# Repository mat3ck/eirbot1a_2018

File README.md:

# eirbot1a_2018

Eirbot first year team project for 2018 France Championship of Robotics 
___
Projet de l'equipe 1A d'Eirbot pour la coupe de France de robotique 2018

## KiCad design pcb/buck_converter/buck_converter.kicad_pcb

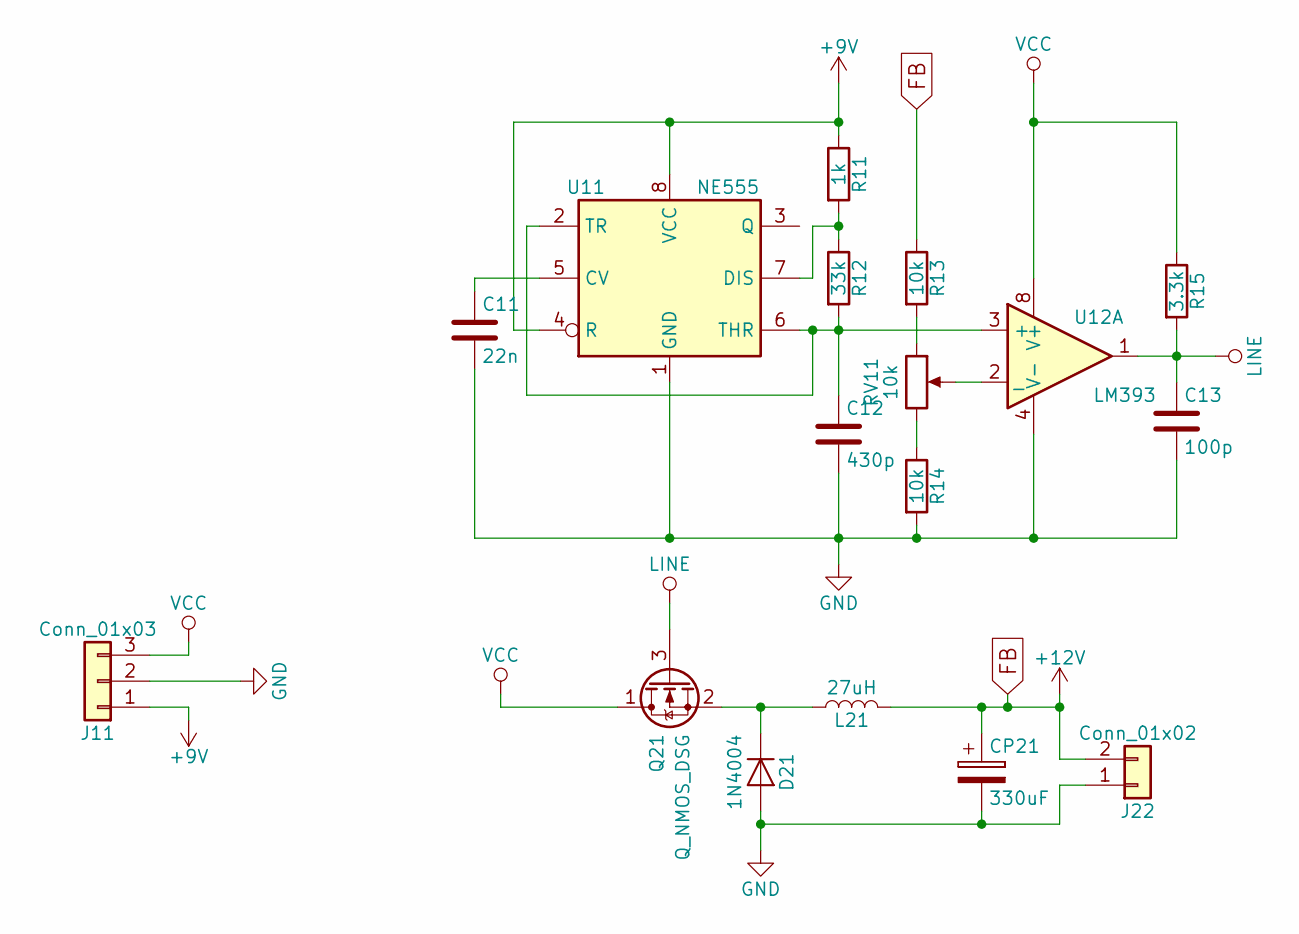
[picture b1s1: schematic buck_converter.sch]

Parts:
C11: 22n; C_0805_HandSoldering
C12: 430p; C_Disc_D4.7mm_W2.5mm_P5.00mm
C13: 100p; C_0805_HandSoldering
CP21: 330uF; CP_Radial_D10.0mm_P5.00mm
D21: 1N4004; D_A-405_P10.16mm_Horizontal
J11: Conn_01x03; PhoenixContact_MC-G_03x3.81mm_Angled
J22: Conn_01x02; PhoenixContact_MC-G_02x3.81mm_Angled
L21: 27uH; L_Radial_D8.7mm_P5.00mm_Fastron_07HCP
Q21: Q_NMOS_DSG; TO-220-3_Vertical
R11: 1k; R_0805_HandSoldering
R12: 33k; R_0805_HandSoldering
R13, R14: 10k; R_0805_HandSoldering
R15: 3.3k; R_0805_HandSoldering
RV11: 10k; Potentiometer_Trimmer_Bourns_3296Y
U11: NE555; DIP-8_W7.62mm_LongPads
U12: LM393; DIP-8_W7.62mm_LongPads

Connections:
+9V: J11.1, R11.1, U11.4 (R), U11.8 (VCC)
FB: CP21.1, J22.2, L21.2, R13.1
GND: C11.2, C12.2, C13.2, CP21.2, D21.2 (A), J11.2, J22.1, R14.2, U11.1 (GND), U12.4 (V-)
LINE: C13.1, Q21.3 (G), R15.2, U12.1
unnamed: C11.1, U11.5 (CV)
unnamed: C12.1, R12.2, U11.2 (TR), U11.6 (THR), U12.3 (+)
unnamed: D21.1 (K), L21.1, Q21.2 (S)
unnamed: R11.2, R12.1, U11.7 (DIS)
unnamed: R13.2, RV11.1
unnamed: R14.1, RV11.3
unnamed: RV11.2, U12.2 (_)
VCC: J11.3, Q21.1 (D), R15.1, U12.8 (V+)

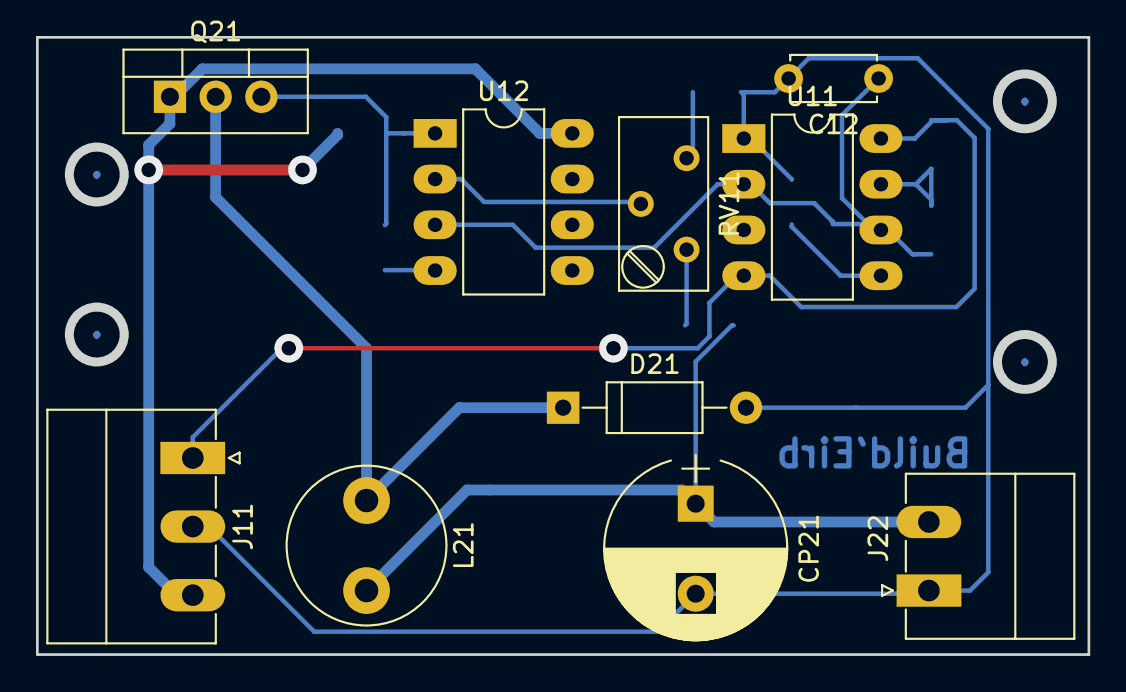
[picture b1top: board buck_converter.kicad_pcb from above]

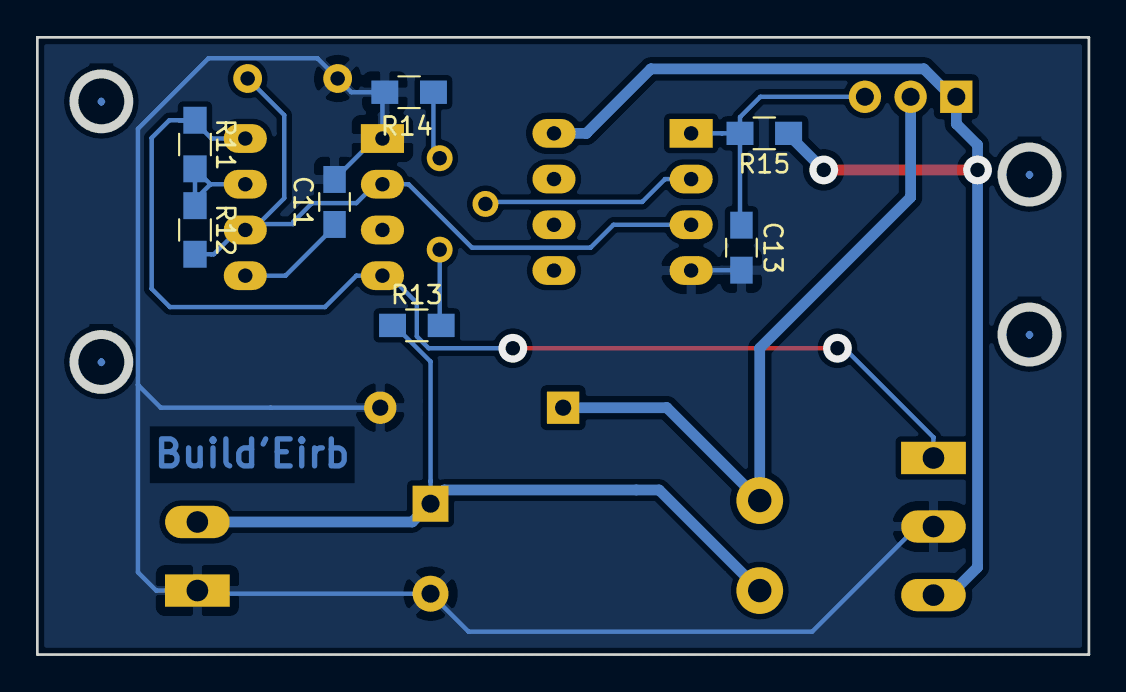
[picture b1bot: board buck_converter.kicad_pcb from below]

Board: 2 copper layers, 58.4 x 34.3 mm, 17 parts (7 on the bottom side), 12 nets.

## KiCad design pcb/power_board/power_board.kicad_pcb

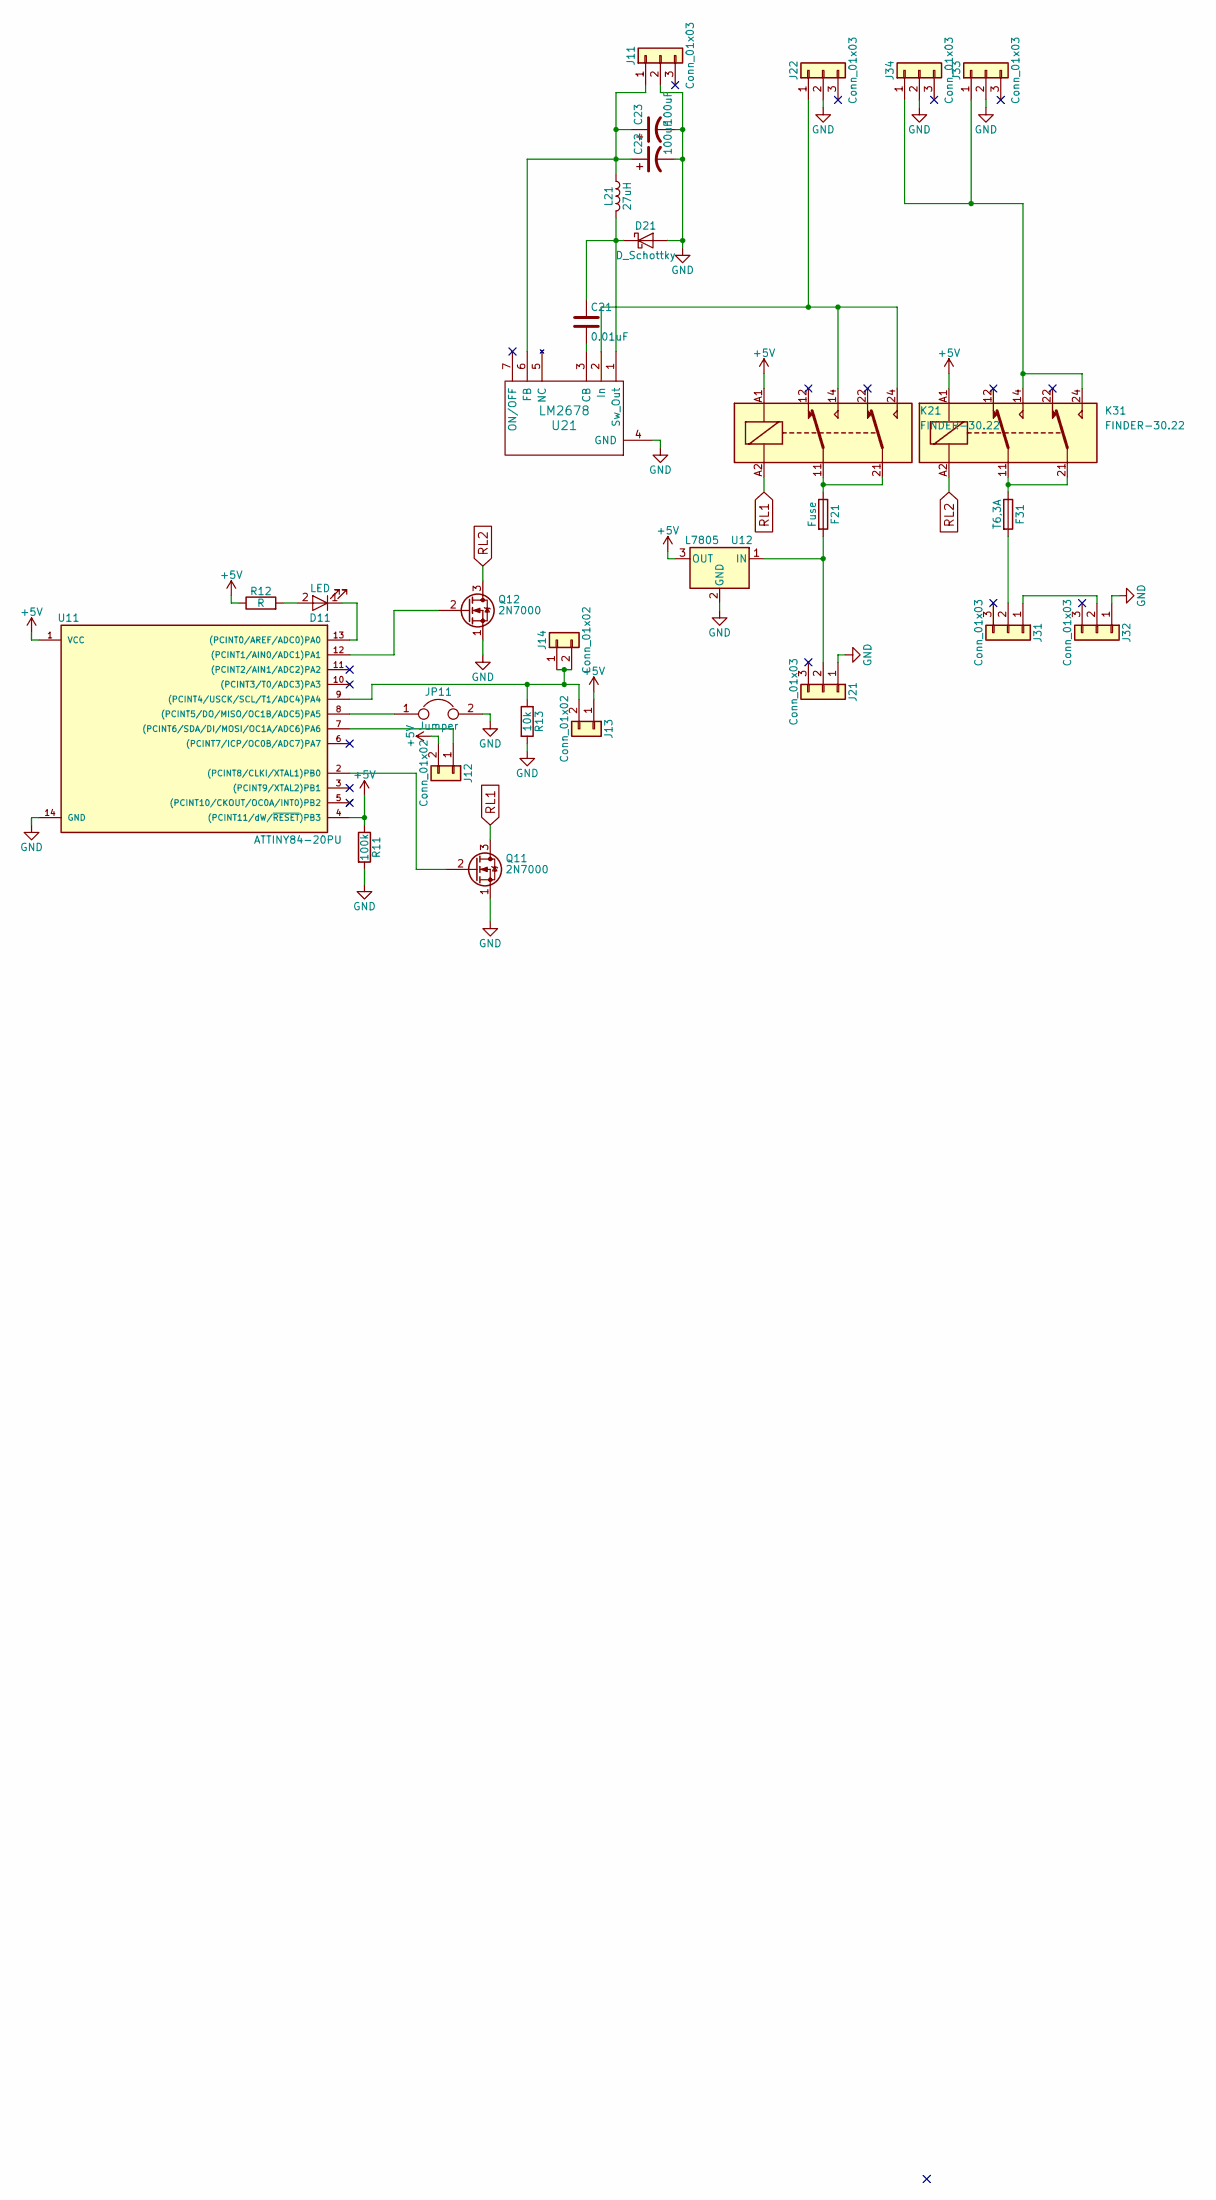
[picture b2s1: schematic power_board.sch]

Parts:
C21: 0.01uF; C_Disc_D4.3mm_W1.9mm_P5.00mm
C22, C23: 100uF; CP_Radial_D6.3mm_P2.50mm
D11: LED; LED_1206_HandSoldering
D21: D_Schottky; D_DO-41_SOD81_P7.62mm_Horizontal
F21: Fuse; Fuseholder5x20_horiz_open_inline_Type-I
F31: T6,3A; Fuseholder5x20_horiz_open_inline_Type-I
J11, J21, J22, J31, J32, J33, J34: Conn_01x03; PhoenixContact_MC-G_03x3.81mm_Angled
J12, J13: Conn_01x02; PhoenixContact_MC-G_02x3.81mm_Angled
J14: Conn_01x02; Pin_Header_Straight_1x02_Pitch2.54mm
JP11: Jumper; Test_Point_2Pads
K21, K31: FINDER-30.22; Relay_DPDT_Finder_40.52
L21: 27uH; L_Radial_D7.8mm_P5.00mm_Fastron_07HCP
Q11, Q12: 2N7000; TO-92_Molded_Narrow
R11: 100k; R_0805_HandSoldering
R12: R; R_0805_HandSoldering
R13: 10k; R_0805_HandSoldering
U11: ATTINY84-20PU; DIP-14_W7.62mm
U12: L7805; TO-220-3_Vertical
U21: LM2678; TO-220-7_Vertical_StaggeredType1

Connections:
+5V: J12.2, J13.1, K21.A1, K31.A1, R11.1, R12.1, U11.1 (VCC), U11.4 ((PCINT11/dW/~RESET~)PB3), U12.3 (OUT)
GND: C22.2, C23.2, D21.2 (A), J11.2, J21.1, J22.2, J32.1, J33.2, J34.2, JP11.2, Q11.1 (S), Q12.1 (S), R11.2, R13.2, U11.14 (GND), U12.2 (GND), U21.4 (GND)
unnamed: C21.1, D21.1 (K), L21.2, U21.1 (Sw_Out)
unnamed: C21.2, U21.3 (CB)
unnamed: C22.1, C23.1, J11.1, L21.1, U21.6 (FB)
unnamed: D11.1 (K), U11.13 ((PCINT0/AREF/ADC0)PA0)
unnamed: D11.2 (A), R12.2
unnamed: F21.1, K21.11, K21.21
unnamed: F21.2, J21.2, U12.1 (IN)
unnamed: F31.1, K31.11, K31.21
unnamed: F31.2, J31.2
unnamed: J12.1, U11.7 ((PCINT6/SDA/DI/MOSI/OC1A/ADC6)PA6)
unnamed: J13.2, J14.1, J14.2, R13.1, U11.9 ((PCINT4/USCK/SCL/T1/ADC4)PA4)
unnamed: J22.1, K21.14, K21.24, U21.2 (In)
unnamed: J31.1, J32.2
unnamed: J33.1, J34.1, K31.14, K31.24
unnamed: JP11.1, U11.8 ((PCINT5/DO/MISO/OC1B/ADC5)PA5)
unnamed: Q11.2 (G), U11.2 ((PCINT8/CLKI/XTAL1)PB0)
unnamed: Q12.2 (G), U11.12 ((PCINT1/AIN0/ADC1)PA1)
RL1: K21.A2, Q11.3 (D)
RL2: K31.A2, Q12.3 (D)

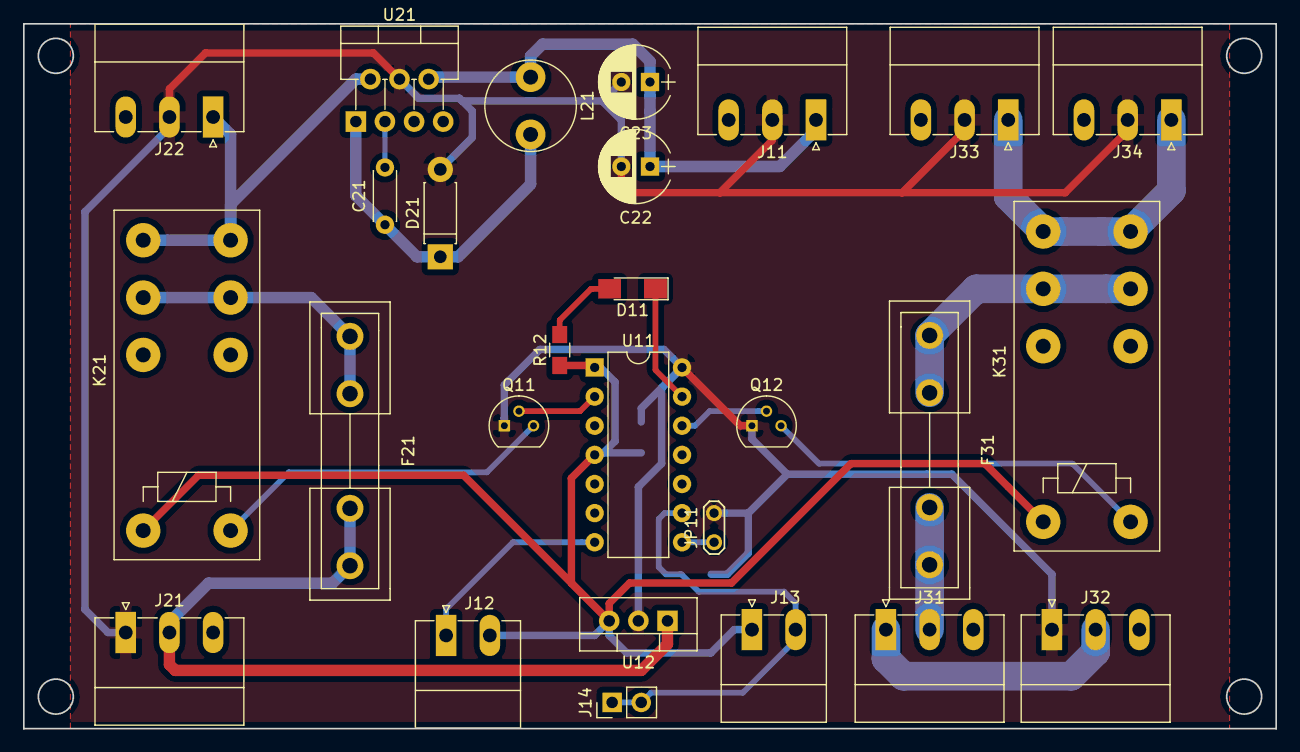
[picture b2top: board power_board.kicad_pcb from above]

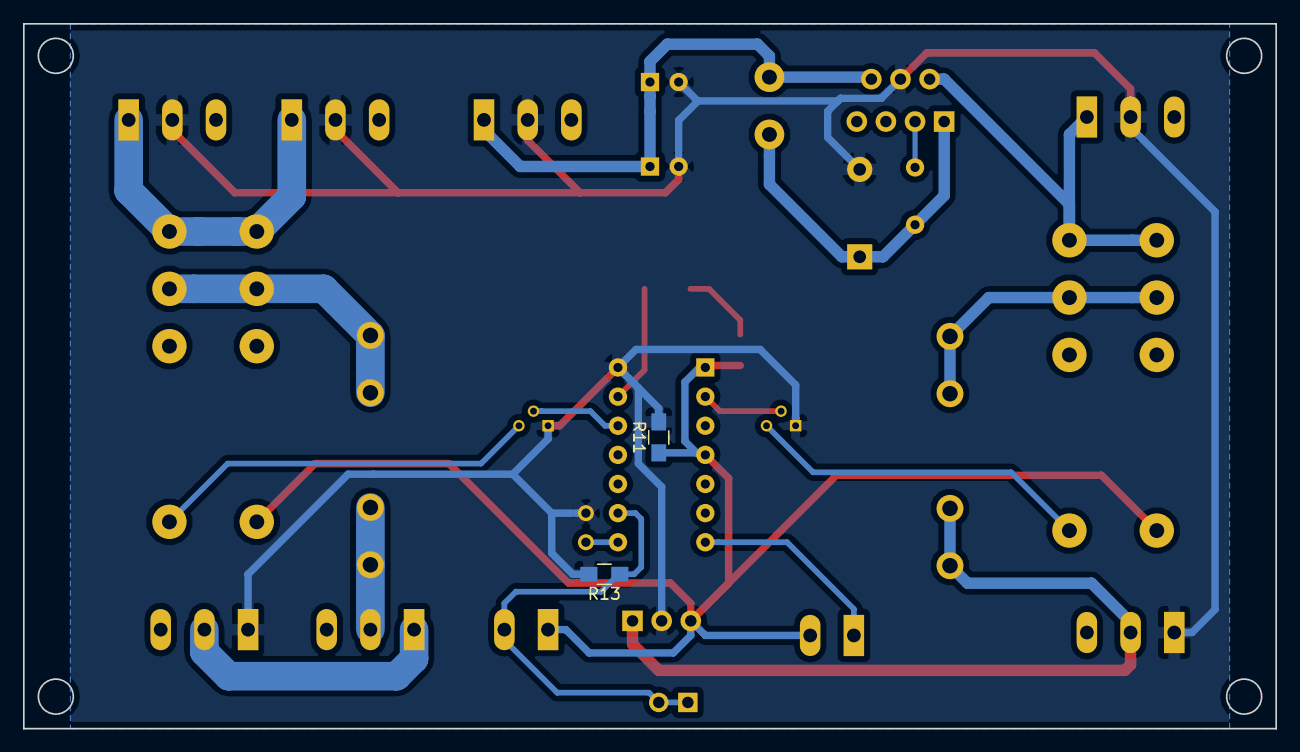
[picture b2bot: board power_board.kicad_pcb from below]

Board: 2 copper layers, 109.2 x 61.5 mm, 29 parts (2 on the bottom side), 21 nets.

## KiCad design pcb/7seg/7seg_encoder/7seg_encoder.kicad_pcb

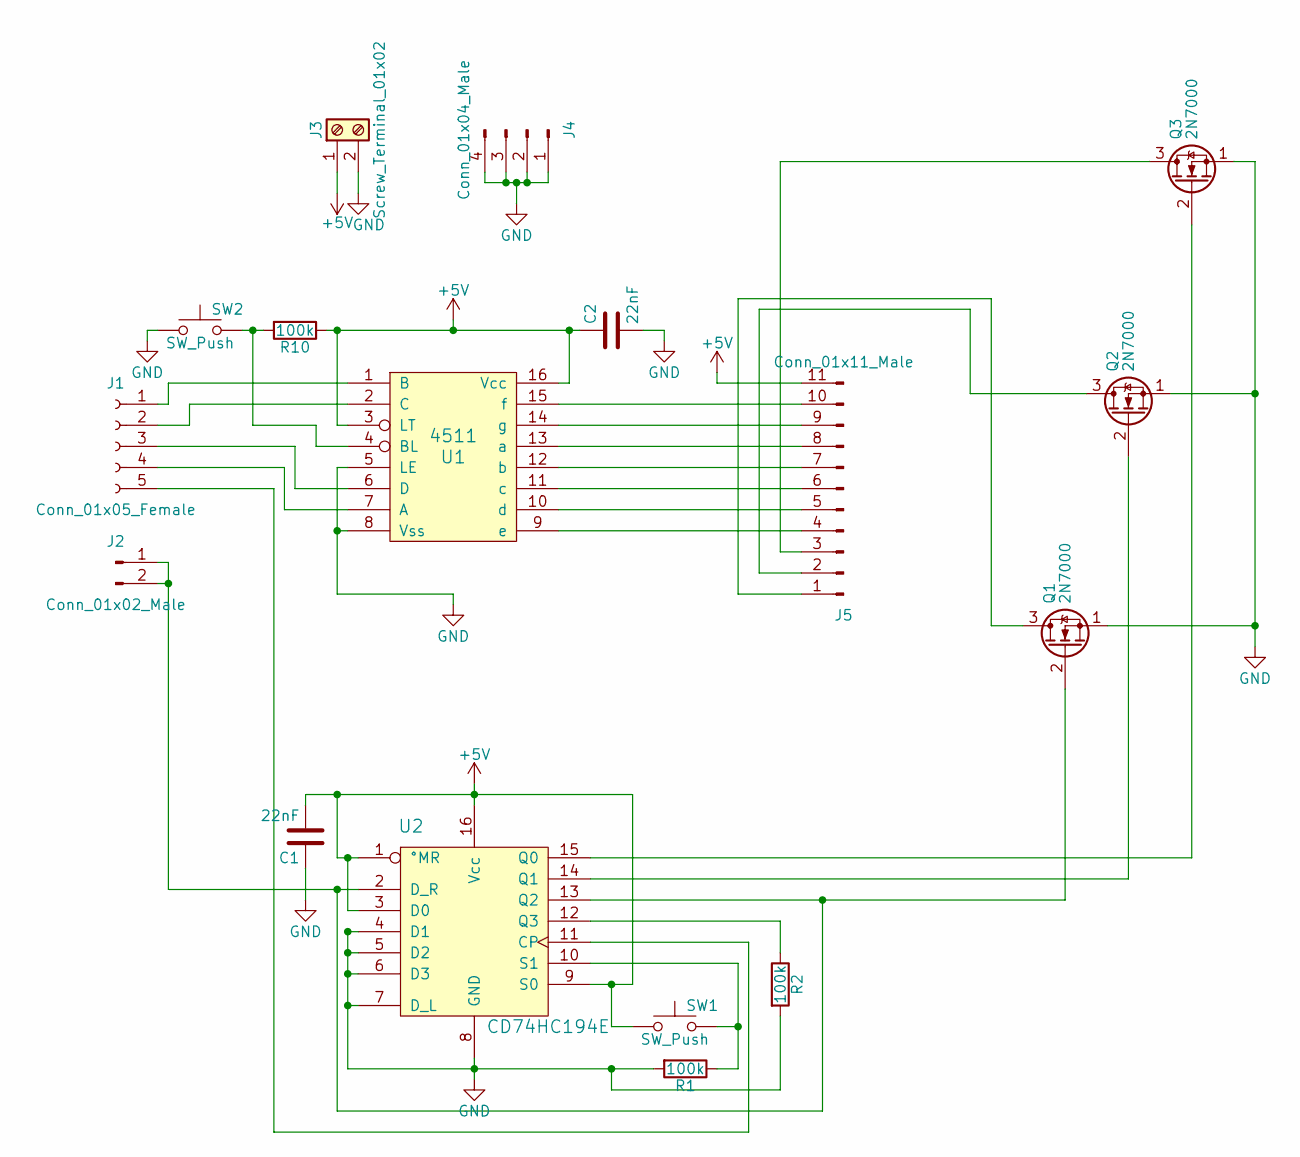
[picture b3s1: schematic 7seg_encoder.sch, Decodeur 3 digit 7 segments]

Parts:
C1, C2: 22nF; C_Disc_D4.3mm_W1.9mm_P5.00mm
J1: Conn_01x05_Female; Socket_Strip_Angled_1x05_Pitch2.54mm
J2: Conn_01x02_Male; Pin_Header_Angled_1x02_Pitch2.54mm
J3: Screw_Terminal_01x02; TerminalBlock_Phoenix_MPT-2.54mm_2pol
J4: Conn_01x04_Male; Pin_Header_Straight_1x04_Pitch2.54mm
J5: Conn_01x11_Male; Pin_Header_Straight_1x11_Pitch2.54mm
Q1, Q2, Q3: 2N7000; TO-92_Molded_Wide
R1, R2, R10: 100k; R_Axial_DIN0204_L3.6mm_D1.6mm_P7.62mm_Horizontal
SW1, SW2: SW_Push; SW_PUSH_6mm
U1: 4511; DIP-16_W7.62mm_Socket
U2: CD74HC194E; SOIC-16_3.9x9.9mm_Pitch1.27mm

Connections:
+5V: C1.2, C2.1, J3.1, J5.11, R10.1, SW1.1, U1.3 (LT), U1.16 (Vcc), U2.1 (°MR), U2.3 (D0), U2.9 (S0), U2.16 (Vcc)
GND: C1.1, C2.2, J3.2, J4.1, J4.2, J4.3, J4.4, Q1.1 (S), Q2.1 (S), Q3.1 (S), R1.2, R2.2, SW2.1, U1.5 (LE), U1.8 (Vss), U2.4 (D1), U2.5 (D2), U2.6 (D3), U2.7 (D_L), U2.8 (GND)
unnamed: J1.1, U1.1 (B)
unnamed: J1.2, U1.2 (C)
unnamed: J1.3, U1.6 (D)
unnamed: J1.4, U1.7 (A)
unnamed: J1.5, U2.11 (CP)
unnamed: J2.1, J2.2, Q1.2 (G), U2.2 (D_R), U2.13 (Q2)
unnamed: J5.1, Q1.3 (D)
unnamed: J5.2, Q2.3 (D)
unnamed: J5.3, Q3.3 (D)
unnamed: J5.4, U1.9 (e)
unnamed: J5.5, U1.10 (d)
unnamed: J5.6, U1.11 (c)
unnamed: J5.7, U1.12 (b)
unnamed: J5.8, U1.13 (a)
unnamed: J5.9, U1.14 (g)
unnamed: J5.10, U1.15 (f)
unnamed: Q2.2 (G), U2.14 (Q1)
unnamed: Q3.2 (G), U2.15 (Q0)
unnamed: R1.1, SW1.2, U2.10 (S1)
unnamed: R2.1, U2.12 (Q3)
unnamed: R10.2, SW2.2, U1.4 (BL)

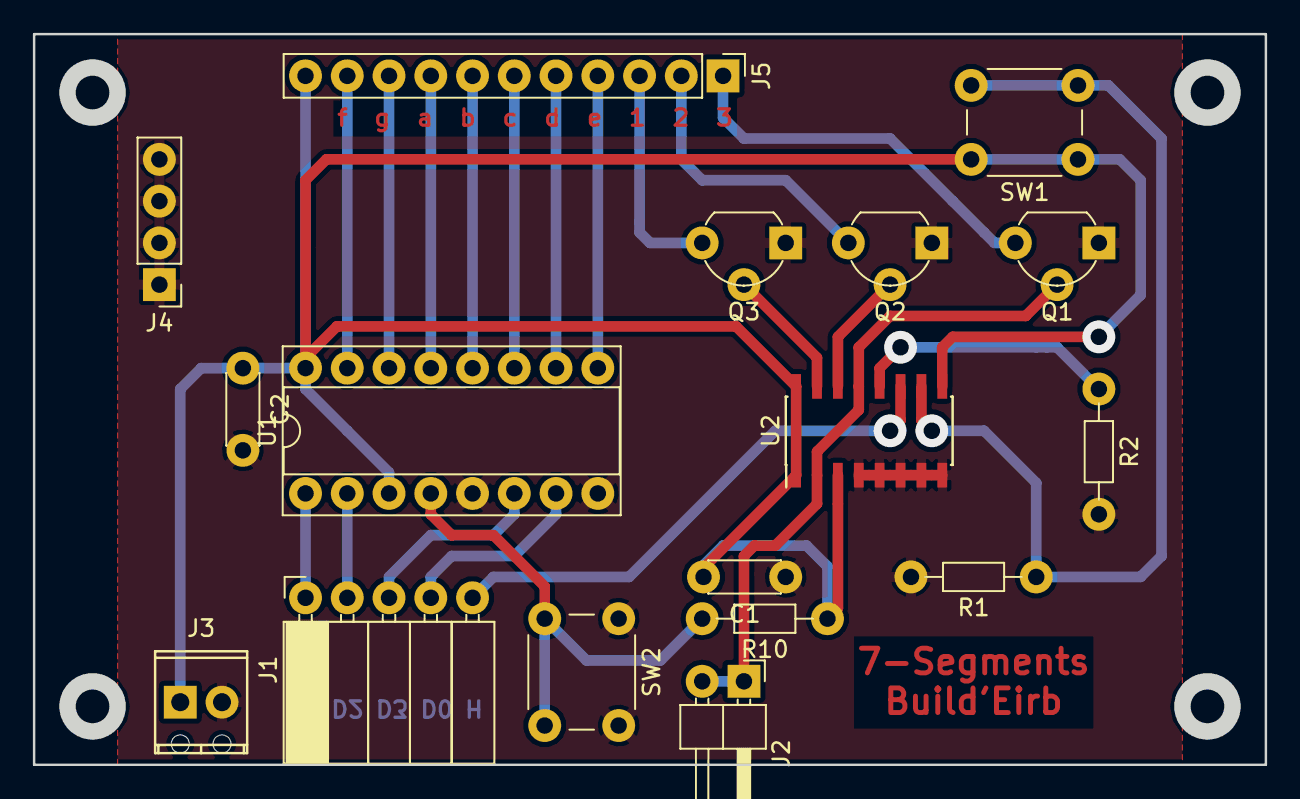
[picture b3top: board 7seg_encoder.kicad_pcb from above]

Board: 2 copper layers, 74.9 x 44.5 mm, 17 parts (0 on the bottom side), 23 nets.

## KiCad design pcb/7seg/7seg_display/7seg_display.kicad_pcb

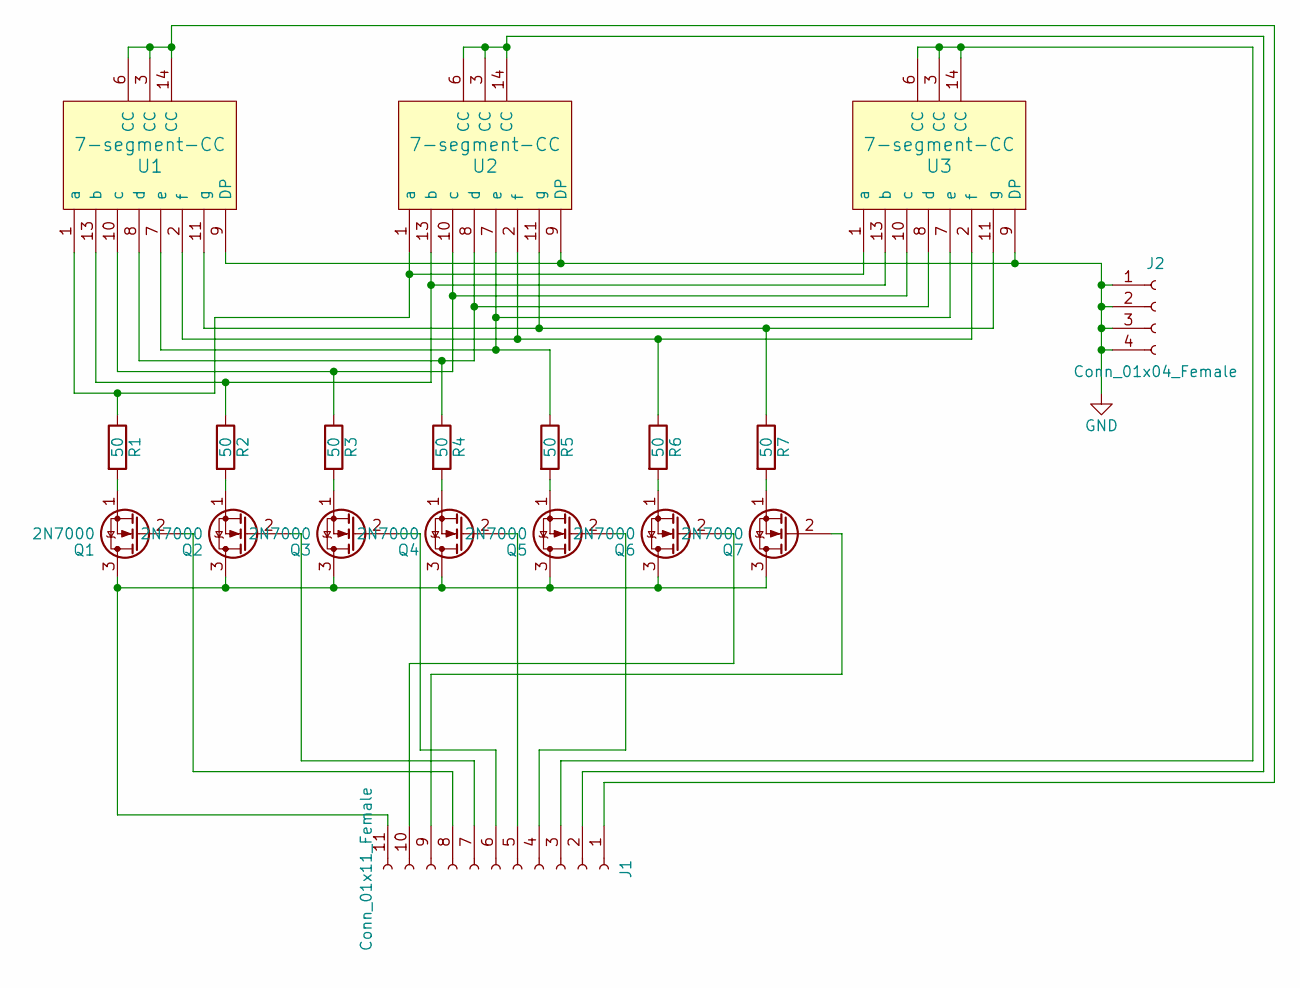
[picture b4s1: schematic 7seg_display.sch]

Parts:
J1: Conn_01x11_Female; Socket_Strip_Straight_1x11_Pitch2.54mm
J2: Conn_01x04_Female; Socket_Strip_Straight_1x04_Pitch2.54mm
Q1, Q2, Q3, Q4, Q5, Q6, Q7: 2N7000; TO-92_Molded_Wide
R1, R2, R3, R4, R5, R6, R7: 50; R_0805_HandSoldering
U1, U2, U3: 7-segment-CC; 7-segment_CC

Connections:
GND: J2.1, J2.2, J2.3, J2.4, U1.9 (DP), U2.9 (DP), U3.9 (DP)
unnamed: J1.1, U1.3 (CC), U1.6 (CC), U1.14 (CC)
unnamed: J1.2, U2.3 (CC), U2.6 (CC), U2.14 (CC)
unnamed: J1.3, U3.3 (CC), U3.6 (CC), U3.14 (CC)
unnamed: J1.4, Q5.2 (G)
unnamed: J1.5, Q4.2 (G)
unnamed: J1.6, Q3.2 (G)
unnamed: J1.7, Q2.2 (G)
unnamed: J1.8, Q1.2 (G)
unnamed: J1.9, Q7.2 (G)
unnamed: J1.10, Q6.2 (G)
unnamed: J1.11, Q1.3 (D), Q2.3 (D), Q3.3 (D), Q4.3 (D), Q5.3 (D), Q6.3 (D), Q7.3 (D)
unnamed: Q1.1 (S), R1.2
unnamed: Q2.1 (S), R2.2
unnamed: Q3.1 (S), R3.2
unnamed: Q4.1 (S), R4.2
unnamed: Q5.1 (S), R5.2
unnamed: Q6.1 (S), R6.2
unnamed: Q7.1 (S), R7.2
unnamed: R1.1, U1.1 (a), U2.1 (a), U3.1 (a)
unnamed: R2.1, U1.13 (b), U2.13 (b), U3.13 (b)
unnamed: R3.1, U1.10 (c), U2.10 (c), U3.10 (c)
unnamed: R4.1, U1.8 (d), U2.8 (d), U3.8 (d)
unnamed: R5.1, U1.7 (e), U2.7 (e), U3.7 (e)
unnamed: R6.1, U1.2 (f), U2.2 (f), U3.2 (f)
unnamed: R7.1, U1.11 (g), U2.11 (g), U3.11 (g)

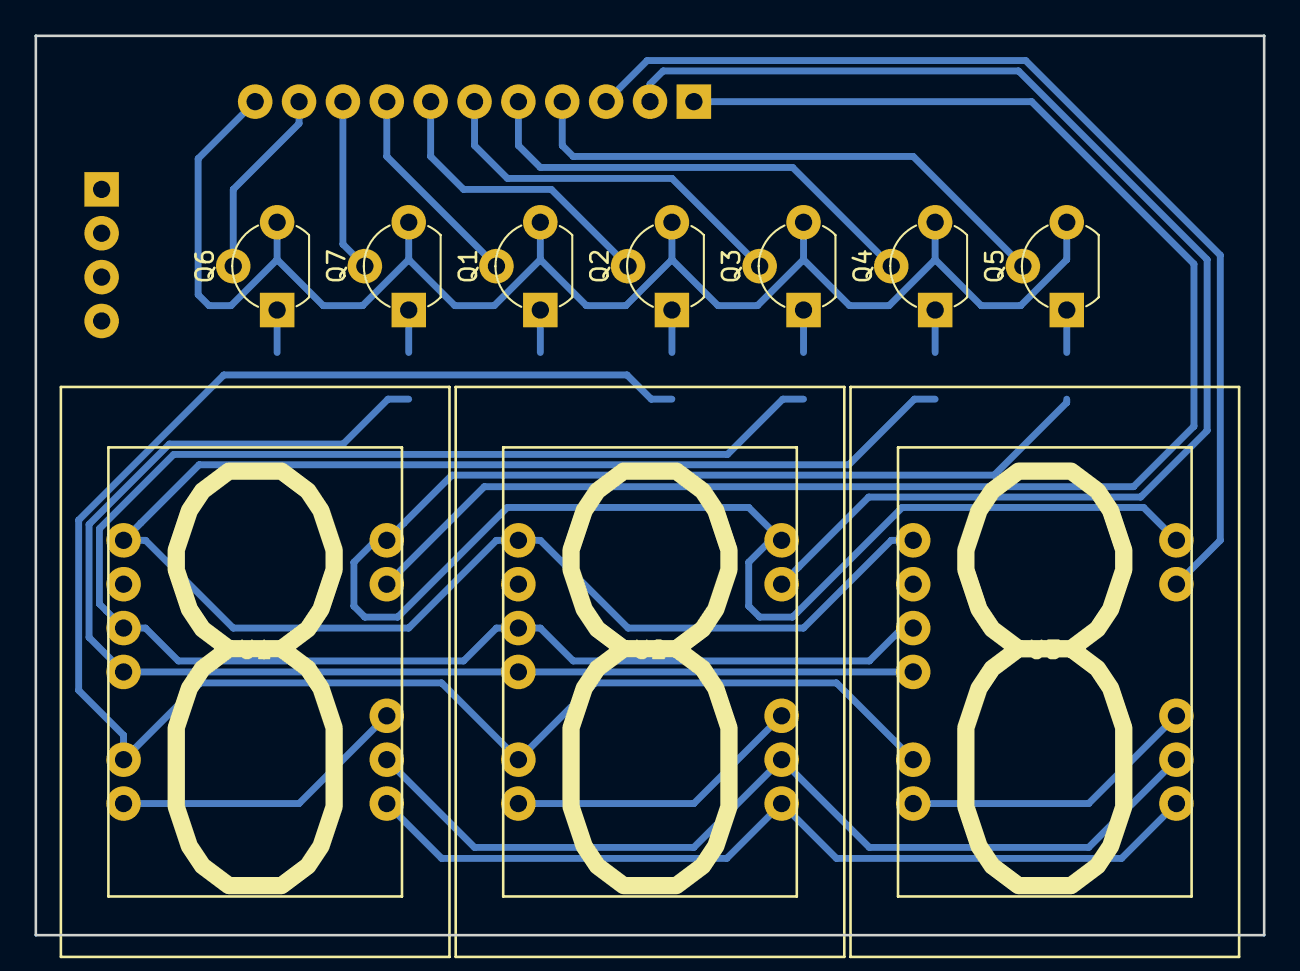
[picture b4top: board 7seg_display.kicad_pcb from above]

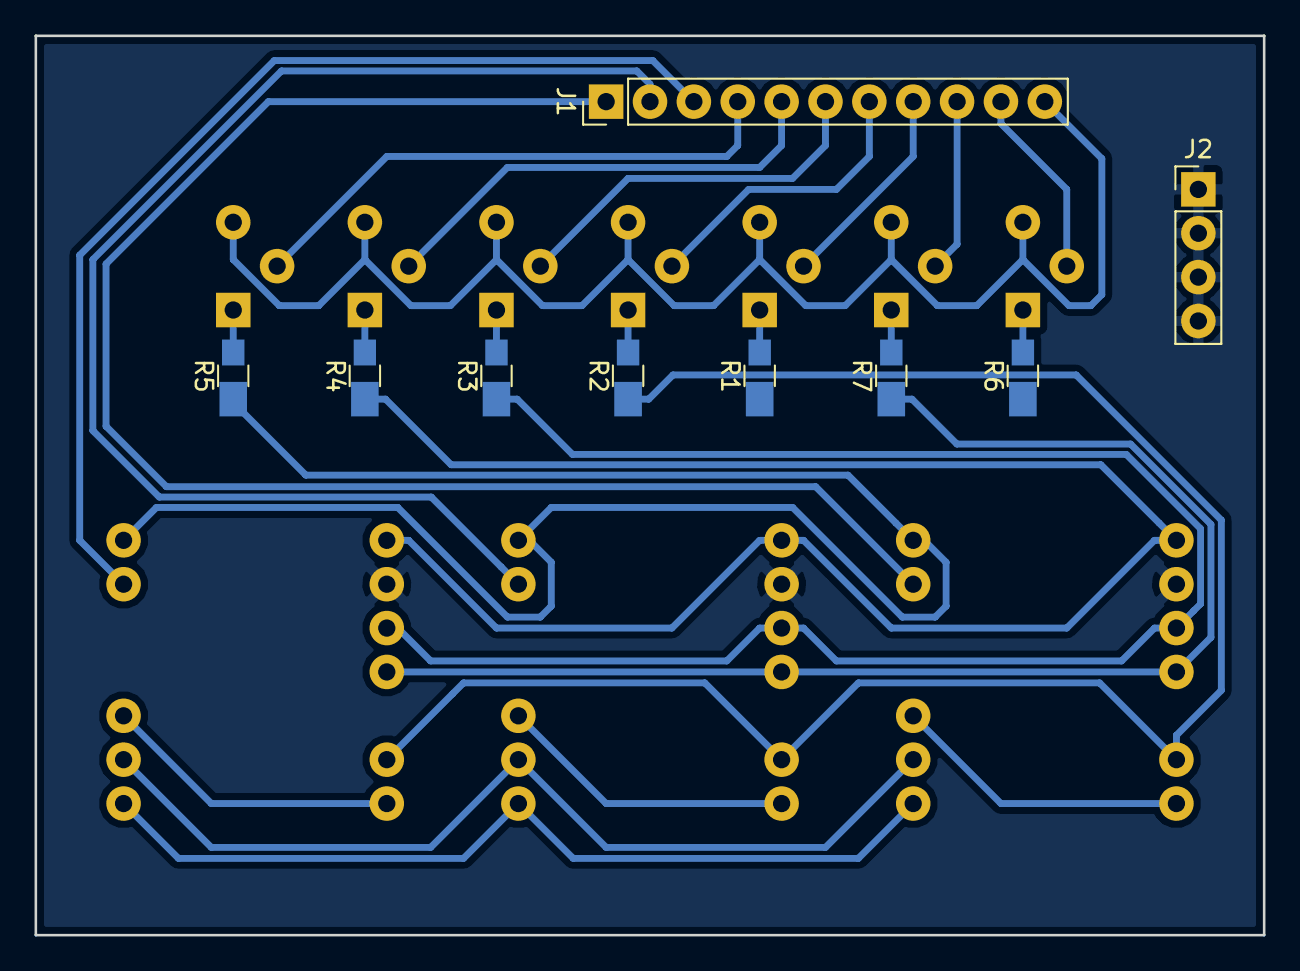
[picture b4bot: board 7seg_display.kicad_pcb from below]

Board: 2 copper layers, 71.1 x 52.1 mm, 19 parts (9 on the bottom side), 26 nets.

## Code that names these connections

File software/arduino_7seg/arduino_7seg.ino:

//Programme de test afficheur 7-segments
#include <SoftwareSerial.h>
SoftwareSerial mySerial(PA7,PA6); //RX TX

int valeur0 = 1;
int valeur1 = 2;
int valeur2 = 7;
int str[] = {0,0,0};

int freq = 100;
int clk = 0b0;
int compteur_aff = 0;

void setup() {
  mySerial.begin(9600);
  pinMode(PA6, OUTPUT); // TX
  pinMode(PA7, INPUT);  // RX
  pinMode(PA0, OUTPUT); // bit0
  pinMode(PA1, OUTPUT); // bit1
  pinMode(PA2, OUTPUT); // bit2
  pinMode(PA3, OUTPUT); // bit3
  pinMode(PA4, OUTPUT); // clk
  pinMode(PA5, INPUT);  // position
}

void loop() {
  if(clk == 0){
    if(digitalRead(PA5))
      compteur_aff == 3;
    if(compteur_aff == 1){
      affichage(valeur0);
    }
    else if(compteur_aff == 2){
      affichage(valeur1);
    }
    else if(compteur_aff == 3){
      affichage(valeur2);
      compteur_aff = 0;
    }
    compteur_aff++;  
  
  }
  clk = ~clk;
  digitalWrite(PA4, clk);
  Event();
  delayMicroseconds(1000000/(7*freq));
}

void affichage(int valeur){
  digitalWrite(PA0, valeur & 0b0001);
  digitalWrite(PA1, valeur & 0b0010); 
  digitalWrite(PA2, valeur & 0b0100);
  digitalWrite(PA3, valeur & 0b1000);
}

void Event(){
  if(mySerial.available() >= 3){ // Envoyer le score dans un char* sous le format "000"
    for(int i=0; i < 3; i++){
      str[i] = mySerial.read() - 48;
    }
    valeur0 = str[0];
    valeur1 = str[1];
    valeur2 = str[2];
    while(mySerial.available() > 0){
      mySerial.read();
    }
  }
}

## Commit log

2017-11-17 Update README.md
    translation, formatting
2018-01-26 Changed makefile to support one exec for each robot
2018-01-26 Added some unfinished libs
2018-01-26 Renames, adding the errors.h filew
2018-01-26 Debugged motors.cpp, types changing
2018-01-26 Changed header protypes and TODO
2018-01-26 Prototype changes in new_motor, creation of pins file for robot1
2018-01-26 Add pins
2018-01-26 Modif gitignore Copper
2018-01-26 Changed gitignore
2018-01-26 Few style changes
2018-01-26 Still few style changes
2018-01-26 Added movement files in libs (unfinished)
2018-01-27 Changed some pointers name
2018-01-27 Changed include conditions
2018-01-27 Added missing files
2018-01-27 Removed some unfinished stuff
2018-01-27 Minor changes
2018-01-27 Debbuged compilation chain
2018-01-27 Just few paging style modifications
2018-01-27 Add basics to robot1.cpp
2018-01-27 changed struct into class for motors
2018-01-28 Made Motor::SetPwm() public
2018-01-28 Indent in motors.h
2018-01-29 Style adjustments in motors.*
2018-01-29 Finished class for qei
2018-01-29 Added qei to robot1.cpp
2018-01-29 Solved some bugs in qei lib, still need testing
2018-01-29 Solved last bugs in qei lib, now fonctionnal
2018-01-29 Added a test main for qei
2018-01-29 Clean main with qei declared
2018-01-29 Just style editing
2018-01-29 Removed old qei libraries
2018-01-29 Created a PID class
2018-01-29 Changed TODO
2018-01-30 Renamed files and put robot specific values in a header
2018-01-30 Changed makefile to add and rename objects
2018-01-30 Changed Pid and Motor classes to make a speed PID, still need work
2018-01-30 Rewrote a clean main with all objects
2018-01-31 Changed types in motor class
2018-01-31 Changed qei lib to be more re-usable
2018-01-31 Changed object order
2018-01-31 Changed motor class to work with tickers instead of timers
2018-01-31 Clean main with tickers for motors
2018-02-01 Changed 'm_' into '_' for class data members
2018-02-01 Made SetPid protected in class Pid
2018-02-01 Include mbed
2018-02-01 Minor changes in Pid and Motor classes
2018-02-01 DO NOT USE, test main to set PID parameters
2018-02-01 Minor changes into clean main
2018-02-04 Renames and added a timer to motor
2018-02-04 Renamed some vars
2018-02-04 Added timers to motors
2018-02-04 Rename some vars
2018-02-04 Fixed an error
2018-02-04 Changed vars names
2018-02-04 Lightened motor class
2018-02-05 Added security to motors
2018-02-05 New block class to command motors at a higher level
2018-02-08 Made motor class simpler, removed security
2018-02-08 Clean main
2018-02-08 New class block to control motors at a higher level
2018-02-08 Added block object to makefile
2018-02-08 Debug
2018-02-08 Changed methods to public
2018-02-08 Clean main with blocks
2018-02-08 Renamed motor pins
2018-02-10 Added PID coef
2018-02-10 Changed PID structure and added circular array class
2018-02-10 Changed call to GetPid to match new definition
2018-02-10 New clean main with PID coef arrays
2018-02-10 Completed ticker def for blocks
2018-02-14 Added GetPwm method to Motor
2018-02-14 Removed timer and changed pid call
2018-02-14 Moved RefreshPid call
2018-02-14 Changed Block constructor arguments
2018-02-15 Added getters
2018-02-15 Changed PID coefficients
2018-02-15 New telemetry function
2018-02-15 New clean main
2018-02-15 Include mbed.h
2018-02-15 Added telemetry to makefile
2018-02-15 Put Pid coef in parenthesis
2018-02-15 Debugged telemetry func
2018-02-15 Added a SetBreak method
2018-02-15 Changed direction type to bool
2018-02-15 Corrected index calculation
2018-02-15 Corrected RefreshDiff
2018-02-15 Changed printf spacings
2018-02-16 Remove static type for a var
2018-02-16 Manage direction for mirror motors
2018-02-16 Changed CArray to pointers in members
2018-02-19 Changed pid period
2018-02-20 Clean main with debug led
2018-02-20 Initial commit of GPI2 class
2018-02-20 Renamed led
2018-02-20 Include new gp2 lib
2018-02-20 Minor changes of style
2018-02-20 test
2018-02-22 Print var_max as a float
2018-02-22 Changed Pid constructor prototype
2018-02-22 Added made varmax absolute
2018-02-22 Initial commit of MBED AX12 librairy, created by Thomas Saliba (ZdTmasar)
2018-02-22 Fixed telemetry function
2018-02-23 Changed TODOs
2018-02-23 Reworked workspace to add more content
2018-02-23 Changes to follow renamings etc
2018-02-23 Renames and adapting makefile
2018-02-23 New folders and empty READMEs
2018-02-23 Changed def name
2018-02-23 Add new clean main and config for nucleo_2
2018-02-25 Added main robot 3d base
2018-02-25 Added side robot 3d base
2018-02-25 Added extensions to gitignore
2018-02-25 Added clamp 3d design
2018-02-25 Added cannon 3d design
2018-02-25 Added 7 segments pcb
2018-02-25 Added 7 segments arduino script
2018-02-25 Renamed main robot folder
2018-02-25 Renamed arudino 7 segments folder
2018-02-25 Added power board pcb design
2018-02-25 Added buck converter pcb design
2018-02-25 Added Arduino power board program
2018-02-25 Added control design and simulations
2018-02-25 Renamed side robot folder
2018-02-25 Added MNT/ to gitignore
2018-02-25 Updated Makefile for new folders names
2018-03-01 Added Block::GetQei(short) and Block::Reset()
2018-03-01 Fixed Block::GetQei() and added qei_value member
2018-03-01 Reworked Motor() to call it with PinNames
2018-03-01 Changed main to follow block and motors rework
2018-03-01 Added Motor::Reset()
2018-03-01 Added Pid::Reset() and CArray::Reset()
2018-03-01 Fixed Pid
2018-03-01 Setup platformio.ini file
2018-03-01 Update gitignore
2018-03-01 Update gitignore v2
2018-03-01 Deleted some parameters from Qei::Qei(), renames
2018-03-01 Added Qei::Reset()
2018-03-01 Completed Block::Reset()
2018-03-01 Added Block::Start() to attach timer on demand
2018-03-01 Use Block::GetQei(short*) instead of RefreshDiff()
2018-03-01 Removed RefreshDiff funct
2018-03-02 PlatformIO ini update
2018-03-02 Completed README to compile nucleo projects
2018-03-02 Updated TODO
2018-03-03 Moved CArray in common.h
2018-03-03 Included common.o to Makefile
2018-03-03 Cleaned dependencies
2018-03-03 Update AX12 lib
2018-03-03 Include error.hpp
2018-03-03 Adding cannon class
2018-03-03 Update code format
2018-03-03 Added different length support to CArray
2018-03-03 Added different length support to Pid class
2018-03-03 Reworked Block to get references as parameters
2018-03-03 Reworked Motor to use constructor initializer list
2018-03-04 Rework using constructor initializer list
2018-03-04 Put parameters name in header prototype
2018-03-04 Use references and removed useless members of Qei
2018-03-04 Renamed ax12 libraries
2018-03-04 Renames and style
2018-03-04 Added all missing libraries to makefile
2018-03-04 Indent style
2018-03-04 Cleaned useless functions and style
2018-03-04 Moved min and max macros in common.hpp
2018-03-04 Fixed README style
2018-03-07 Fixed a Block::Refresh bug
2018-03-08 Support different coeff numbers between error and sp
2018-03-08 Changed MAX_DUTY
2018-03-08 Added min and max functions
2018-03-09 Added min and max function
2018-03-09 Changed reset direction
2018-03-09 New main to test pid
2018-03-13 Changed references into pointers in Pid()
2018-03-13 Added 1m pid test
2018-03-13 Regrouped left and right pid coef
2018-03-13 Main to get transfer functions of the motors
2018-03-13 Clean main with new config file
2018-03-13 Block::GetQei(short*) become Block::GetQei(short&)
2018-03-13 Changed duty default value and Start() function
2018-03-13 Renamed Motor::GetPwm() into Motor::GetDuty()
2018-03-13 Added parameters names into methods prototypes
2018-03-13 Refresh period is now a constructor parameter
2018-03-13 Moved REFRESH_PERIOD into config and changed calls of Block()
2018-03-13 Moved constants and allow choosing pwm period
2018-03-13 Added motors parameters
2018-03-13 Added max_duty as a parameter
2018-03-13 New clean main with new constructors and constants names
2018-03-14 Added transfer function capture files
2018-03-14 Added pwm duty and voltage into files
2018-03-14 Add pins for the cannon
2018-03-14 Unfinished : Added Navigator
2018-03-15 Added Pos class
2018-03-15 Added Pos::Reset()
2018-03-15 Removed ticker from Block
2018-03-15 Made Reset void
2018-03-15 Removed telemetry from include
2018-03-15 Included Navigator to makefile
2018-03-15 Finished navigator class
2018-03-15 Set thresholds
2018-03-15 add support for Timer3
2018-03-16 Fixed RefreshPos()
2018-03-16 Clean main including navigator
2018-03-17 Fixed missing initialization of len_err and len_sp
2018-03-17 Changed motor directions
2018-03-17 Allow different period for pos and pid, fixed signe problems
2018-03-17 Added pi constant
2018-03-17 Navigator with 2 cases on 3 working
2018-03-17 New config
2018-03-17 Clean main with navigator
2018-03-17 Navigator test main
2018-03-18 Changed some int into float
2018-03-28 Improved conditionnal movements
2018-03-28 Changed Qei pins
2018-04-30 Removed useless line
2018-04-30 Reworked navigator, added pause
2018-04-30 New main and config
2018-04-30 Clean main with navigator initialized
2018-05-02 Changed motor dir and pwm max duty
2018-05-02 Clean main with navigator pause
2018-05-02 Added regulation test functions
2018-05-02 Added regulation to Makefile
2018-05-04 Add pins configuration for MIR robot
2018-05-05 Changed closedLoop prototype
2018-05-05 Fixed closed loop regulation function
2018-05-05 Improved time printing
2018-05-05 New PID parameters and motor direction
2018-05-05 Moved ComputeSpeed in common
2018-05-07 Fixed ComputeSpeed()
2018-05-07 Added distQuadRamp()
2018-05-07 Moved ramp parameters in header and changed ComputeSpeed() call
2018-05-09 sir configuration + QEI reconfiguration
2018-05-09 Added Pause func
2018-05-09 add mir config for qei
2018-05-09 Added Pause function
2018-05-09 Improved Navigator
2018-05-09 Changed var name
2018-05-09 Changed Qei declaration
2018-05-10 Added func file
2018-05-31 Lasts modifications made during France Robotic Championship
2018-05-31 Added identifications files
